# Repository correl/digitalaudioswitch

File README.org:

#+title: Audio Input and Volume Control

[[file:finished.jpg]]

* Features
- Switches between three external inputs, outputting through the 3.5mm LINE OUT
  jack.
- Volume control and input switching can be done using the pressable dial on the front
- Current status is displayed on a 128x32 OLED display
- Can be fully controlled via Home Assistant as an [[https://www.home-assistant.io/integrations/mqtt/][MQTT-discoverable]] device.
* Firmware
** Configuration
Create a file named =settings.json= in the project directory with WiFi and MQTT
connection information.

#+begin_src js
  {
      "wifi": {
          "ssid": "MY-SSID",
          "password": "my-wifi-password"
      },
      "mqtt": {
          "broker": "192.168.1.123",
          "prefix": "digital-audio-switch"
      }
  }
#+end_src
** Deploying
Connect the ESP32 to your computer. If you haven't already, [[https://micropython.org/download/esp32/][flash it with the
latest version of MicroPython]], and ensure you have [[https://docs.micropython.org/en/latest/reference/mpremote.html][mpremote installed]].

Running =make= will install dependencies and copy the code and configuration to
the ESP32, resetting it when done.
* Circuit Design
[[file:pcb.png]]

The schematic and board layout can be found in the [[file:kicad/][kicad]] folder.
* Case
[[file:case.png]]

The 3D-printable case is built using FreeCAD and can be found in the [[file:freecad/][freecad]]
folder. It is divided into a top and bottom piece. The PCB is affixed using four
M3 threaded inserts and 6mm M3 bolts, the case is assembled using 2 M3 threaded
inserts and 2 10mm M3 bolts.

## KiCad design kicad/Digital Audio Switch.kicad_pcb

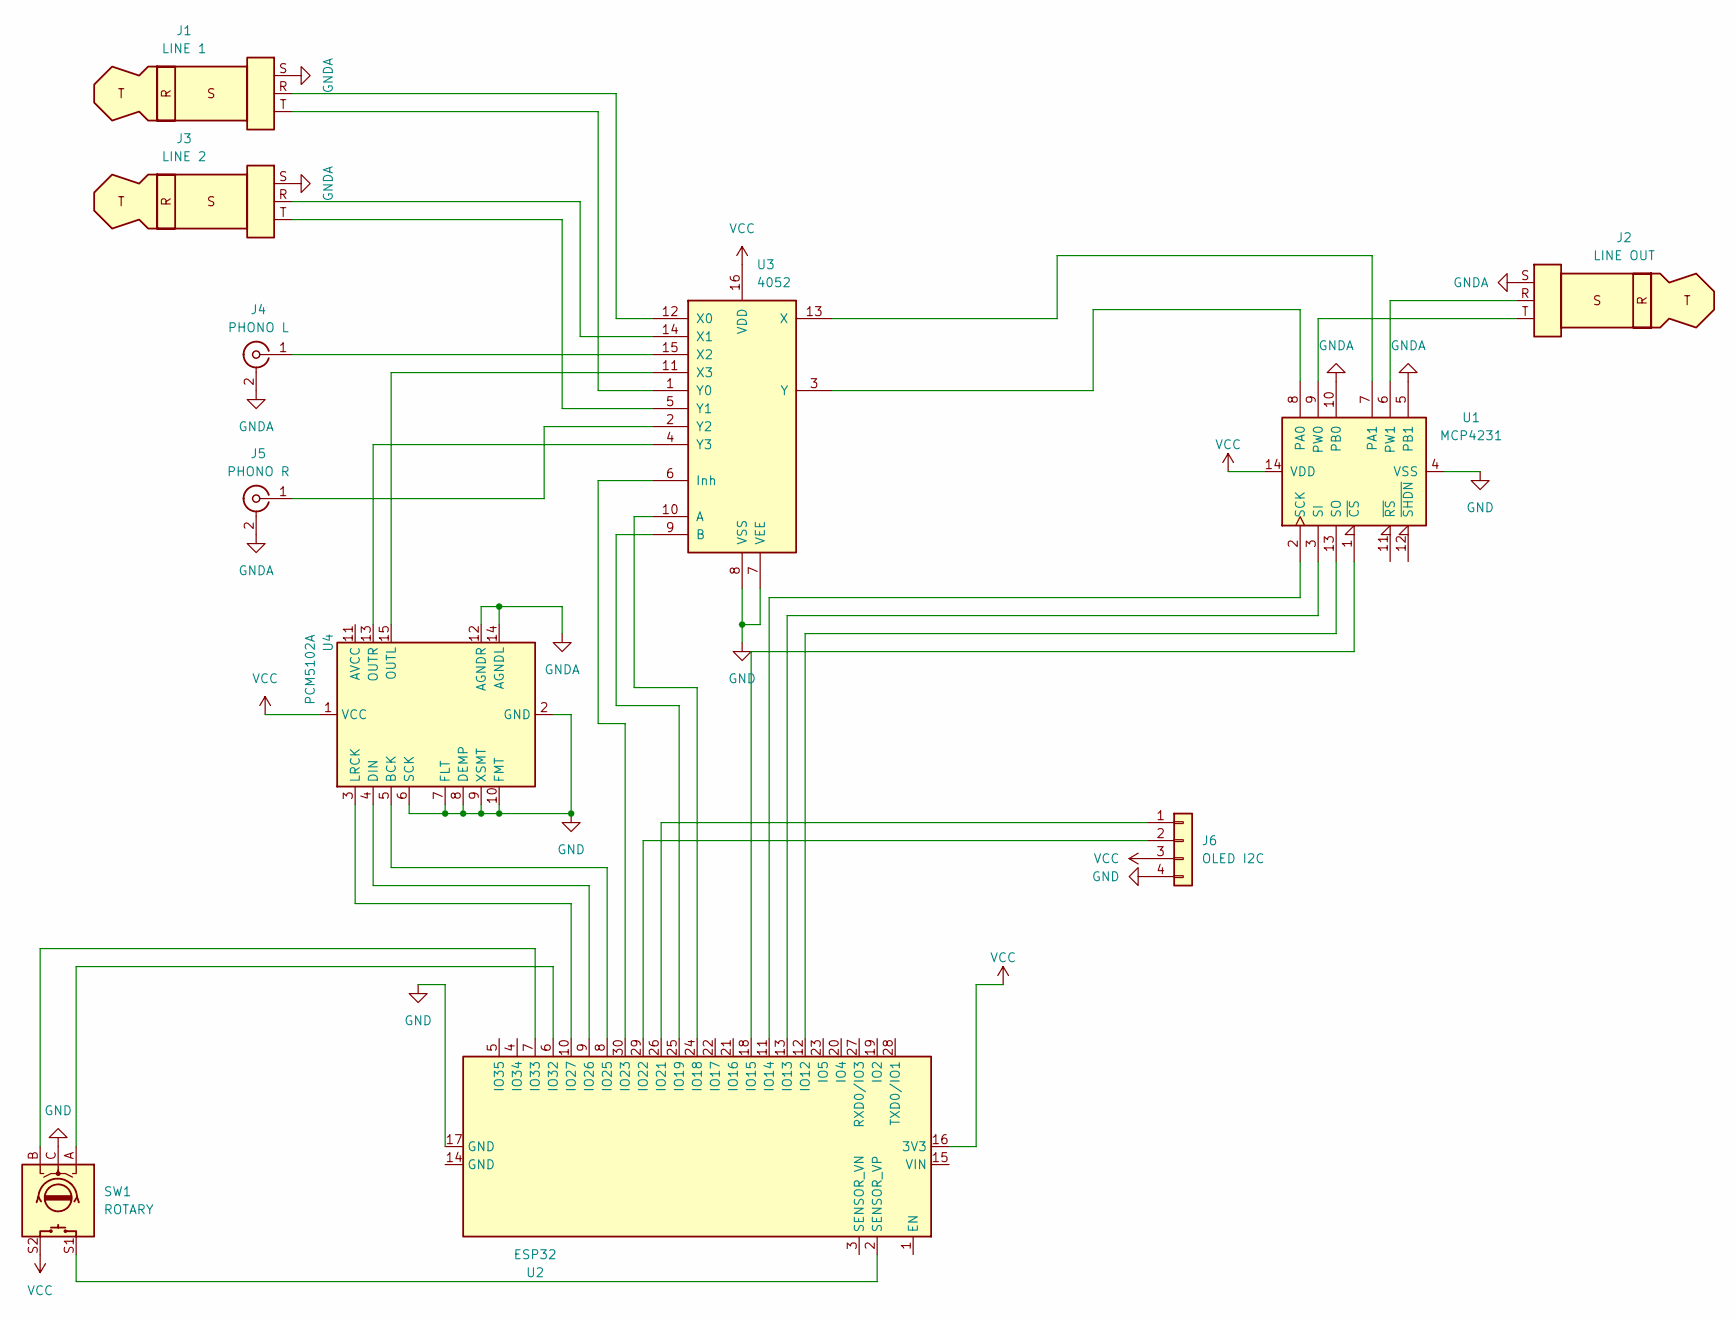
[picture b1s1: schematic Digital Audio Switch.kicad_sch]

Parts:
J1: LINE 1; Jack_3.5mm_CUI_SJ1-3533NG_Horizontal
J2: LINE OUT; Jack_3.5mm_CUI_SJ1-3533NG_Horizontal
J3: LINE 2; Jack_3.5mm_CUI_SJ1-3533NG_Horizontal
J4: PHONO L; KLPX-0848A
J5: PHONO R; KLPX-0848A
J6: OLED I2C; I2C Pin Header
SW1: ROTARY; RotaryEncoder_Bourns_Horizontal_PEC12R-2xxxF-Sxxxx
U1: MCP4231; DIP-14_W10.16mm
U2: ESP32; esp32_devkit_v1_doit
U3: 4052; DIP-16_W10.16mm
U4: PCM5102A; PCM5102

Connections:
GND: J6.4, SW1.C, U1.4 (VSS), U2.17 (GND), U3.7 (VEE), U3.8 (VSS), U4.2 (GND), U4.6 (SCK), U4.7 (FLT), U4.8 (DEMP), U4.9 (XSMT), U4.10 (FMT)
GNDA: J1.S, J2.S, J3.S, J4.2 (Ext), J5.2 (Ext), U1.5 (PB1), U1.10 (PB0), U4.12 (AGNDR), U4.14 (AGNDL)
unnamed: J4.1 (In), U3.15 (X2)
unnamed: J5.1 (In), U3.2 (Y2)
unnamed: J6.1, U2.26 (IO21)
unnamed: J6.2, U2.29 (IO22)
unnamed: U1.8 (PA0), U3.3 (Y)
unnamed: U1.7 (PA1), U3.13 (X)
unnamed: J2.T, U1.9 (PW0)
unnamed: J2.R, U1.6 (PW1)
unnamed: U1.2 (SCK), U2.11 (IO14)
unnamed: U1.3 (SI), U2.13 (IO13)
unnamed: U1.13 (SO), U2.12 (IO12)
unnamed: U1.1 (~CS), U2.18 (IO15)
unnamed: U2.24 (IO18), U3.10 (A)
unnamed: U2.25 (IO19), U3.9 (B)
unnamed: U2.30 (IO23), U3.6 (Inh)
unnamed: U2.8 (IO25), U4.5 (BCK)
unnamed: U2.9 (IO26), U4.4 (DIN)
unnamed: U2.10 (IO27), U4.3 (LRCK)
unnamed: SW1.A, U2.6 (IO32)
unnamed: SW1.B, U2.7 (IO33)
unnamed: SW1.S1, U2.2 (SENSOR_VP)
unnamed: J1.R, U3.12 (X0)
unnamed: J3.R, U3.14 (X1)
unnamed: U3.11 (X3), U4.15 (OUTL)
unnamed: J1.T, U3.1 (Y0)
unnamed: J3.T, U3.5 (Y1)
unnamed: U3.4 (Y3), U4.13 (OUTR)
VCC: J6.3, SW1.S2, U1.14 (VDD), U2.16 (3V3), U3.16 (VDD), U4.1 (VCC)

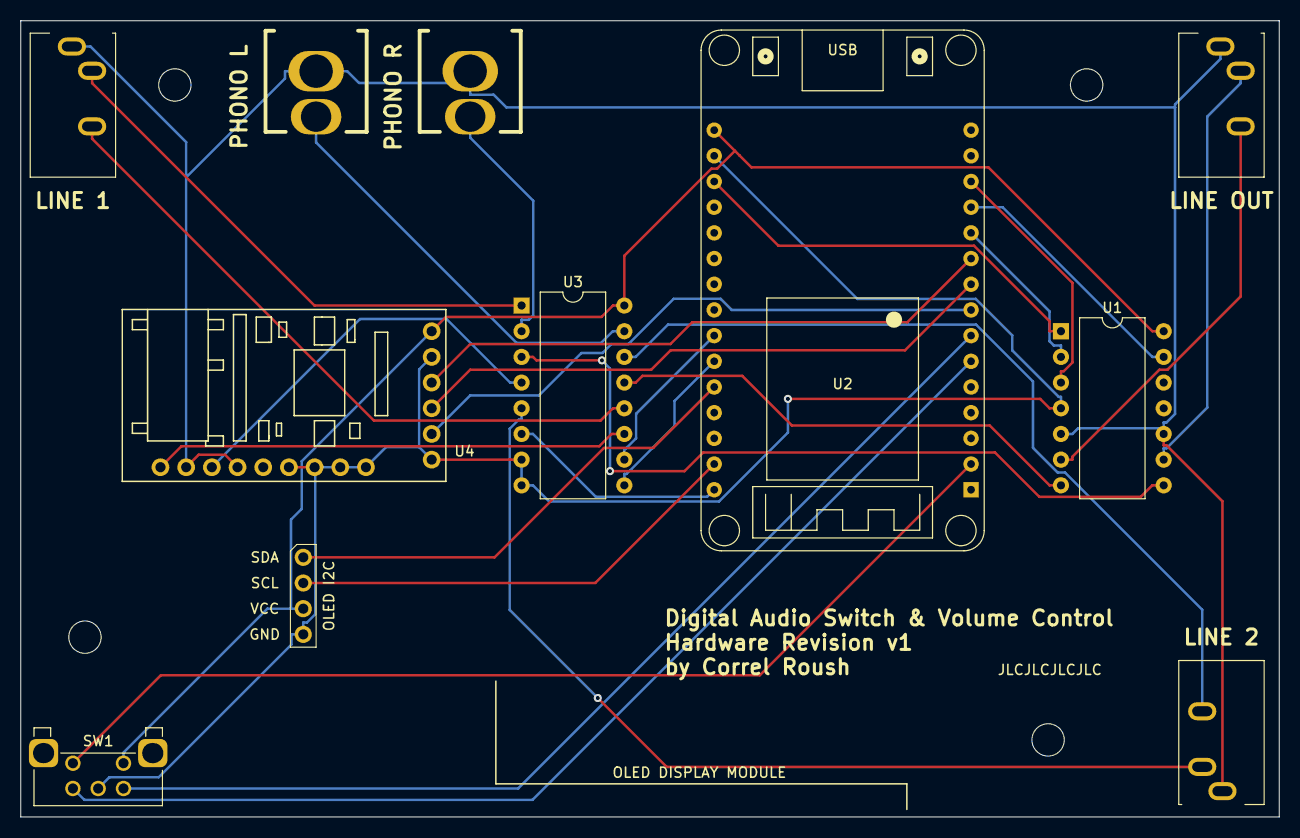
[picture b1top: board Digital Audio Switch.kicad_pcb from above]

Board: 2 copper layers, 124.5 x 78.7 mm, 15 parts (0 on the bottom side), 30 nets.

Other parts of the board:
H1, H2, H3, H4: MountingHole_3.2mm_M3

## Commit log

2023-05-18 Add MQTT controls
2023-05-18 Add tests
2023-05-18 Add Makefile
2023-05-18 Add logging
2023-05-18 Abstract state change tracking
2023-05-18 Mark as offline when the MQTT connection is lost
2023-05-18 Remove repl from the Makefile
2023-05-18 Draw volume levels as horizontal bars
2023-05-27 Add rotary knob volume control
2023-05-28 Add multiplexing switch
2023-05-28 Update switch select log message
2023-05-28 Add MQTT controls for channel and mute
2023-05-28 Add mute and channel status to display
2023-05-28 Only display muted status when actually muted
2023-05-28 Add mute and input switching button controls
2023-06-05 Add KiCad design
2023-06-05 Polish PCB design
2023-06-06 Set gerber export settings
2023-06-06 Ignore generated gerber files
2023-06-06 Add initial OpenSCAD case files
2023-06-06 Generate a basic case bottom with PCB mounting holes
2023-06-07 Add multiple export options to the case design
2023-06-07 Add README
2023-06-08 Add additional part models
2023-06-08 Add audio jack 3d model
2023-06-08 Add an initial case design in FreeCAD
2023-06-13 Update case design with split top and bottom
2023-06-17 Polish up the freecad case
2023-06-17 Set the rotary increment to 4, 1 is way too slow
2023-06-17 Update readme to reference the FreeCAD case design
2023-07-08 Handle MQTT connection failures
2023-07-08 Reconnect when WiFi lacks a valid IP address
2023-07-20 Fix channel labels
2023-09-08 Add additional pictures

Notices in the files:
kicad/Digital Audio Switch.kicad_pcb:
https://creativecommons.org/licenses/by/4.0
License: CC BY 4.0
